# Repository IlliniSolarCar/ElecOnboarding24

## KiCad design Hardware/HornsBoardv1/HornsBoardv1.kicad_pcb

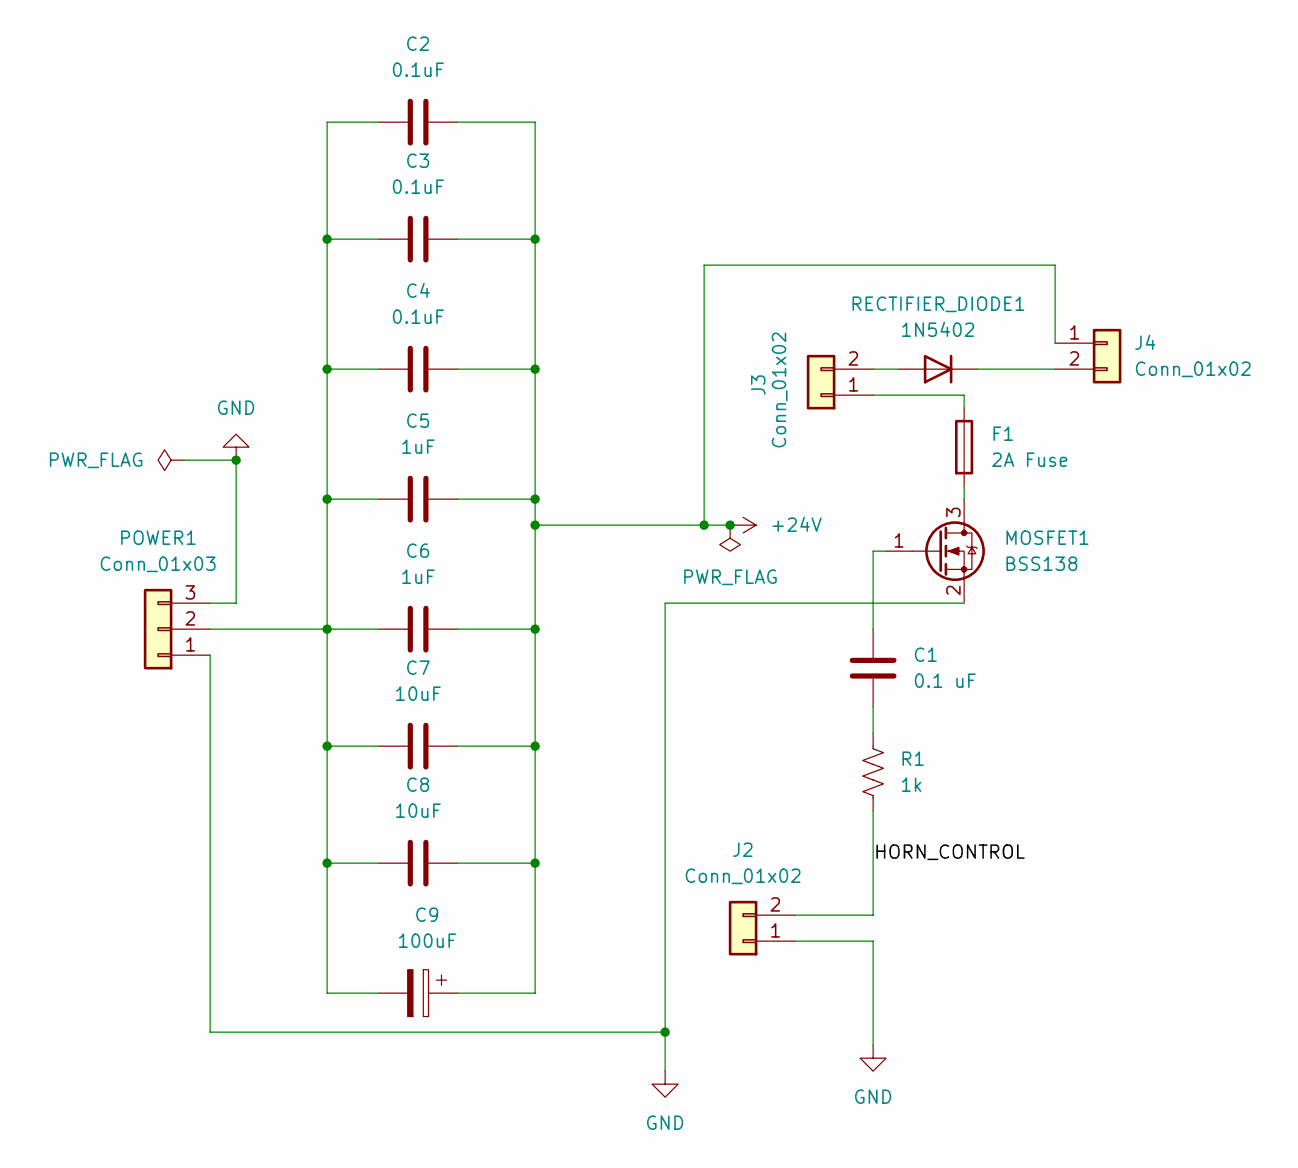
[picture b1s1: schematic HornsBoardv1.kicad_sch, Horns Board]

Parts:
C1: 0.1 uF; CP_Elec_6.3x3
C2, C3, C4: 0.1uF; CP_Elec_6.3x3
C5, C6: 1uF; CP_Elec_6.3x3
C7, C8: 10uF; CP_Elec_6.3x3
C9: 100uF; CP_Elec_6.3x3
F1: 2A Fuse; Fuse_0402_1005Metric_Pad0.77x0.64mm_HandSolder
J2, J3, J4: Conn_01x02; Molex_KK-254_AE-6410-02A_1x02_P2.54mm_Vertical
MOSFET1: BSS138; SOT-23
POWER1: Conn_01x03; Molex_KK-254_AE-6410-03A_1x03_P2.54mm_Vertical
R1: 1k; R_0603_1608Metric_Pad0.98x0.95mm_HandSolder
RECTIFIER_DIODE1: 1N5402; D_DO-201AD_P15.24mm_Horizontal; MPN 1N5402

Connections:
+24V: C2.2, C3.2, C4.2, C5.2, C6.2, C7.2, C8.2, C9.1, J4.1
/HORN_CONTROL: J2.2, R1.2
GND: J2.1, MOSFET1.2 (S), POWER1.1, POWER1.3
unnamed: C1.2, R1.1
unnamed: F1.1, J3.1
unnamed: J3.2, RECTIFIER_DIODE1.2 (A)
unnamed: J4.2, RECTIFIER_DIODE1.1 (K)
unnamed: F1.2, MOSFET1.3 (D)
unnamed: C1.1, MOSFET1.1 (G)
unnamed: C2.1, C3.1, C4.1, C5.1, C6.1, C7.1, C8.1, C9.2, POWER1.2

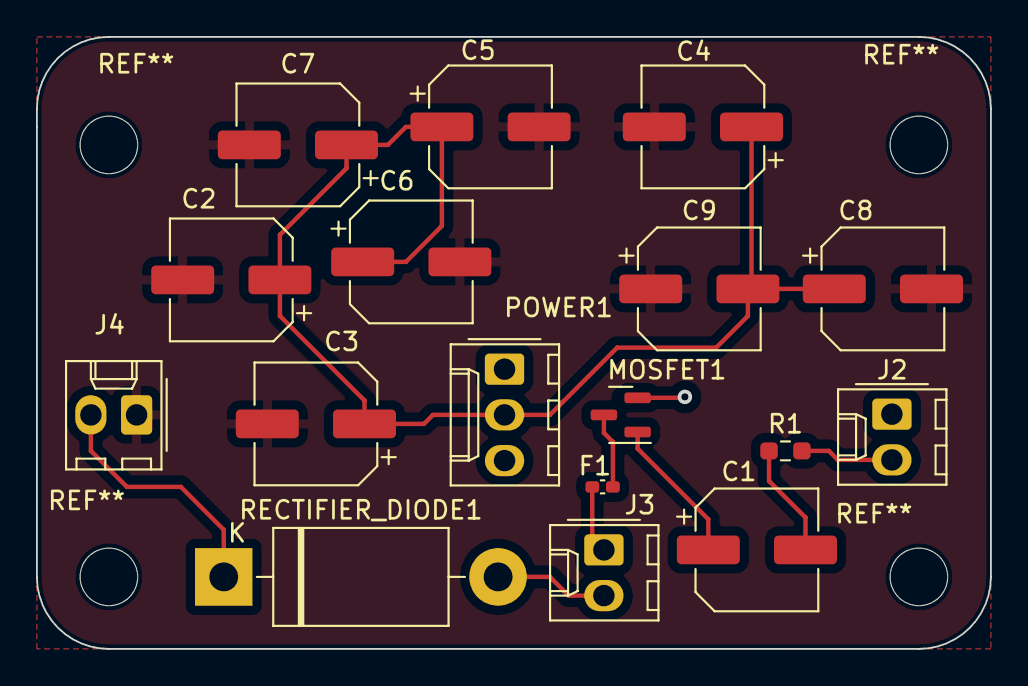
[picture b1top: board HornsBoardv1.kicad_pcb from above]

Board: 2 copper layers, 53.0 x 34.0 mm, 17 parts (0 on the bottom side), 10 nets.

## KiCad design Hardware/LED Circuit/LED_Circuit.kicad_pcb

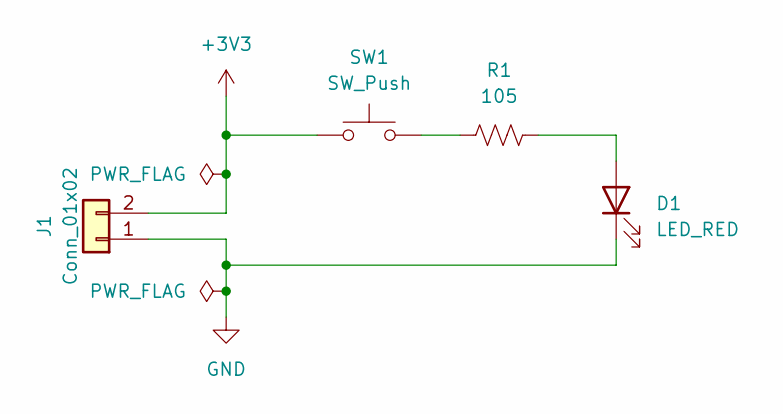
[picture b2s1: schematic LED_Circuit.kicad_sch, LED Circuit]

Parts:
D1: LED_RED; LED_0603_Symbol_on_F.SilkS
J1: Conn_01x02; Molex_KK-254_AE-6410-02A_1x02_P2.54mm_Vertical; MPN 022272021
R1: 105; R_0603_1608Metric_Pad0.98x0.95mm_HandSolder
SW1: SW_Push; SW_DIP_SPSTx01_Slide_6.7x4.1mm_W8.61mm_P2.54mm_LowProfile; MPN 1825910-6

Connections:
+3V3: J1.2, SW1.1
GND: D1.1 (K), J1.1
unnamed: D1.2 (A), R1.2
unnamed: R1.1, SW1.2

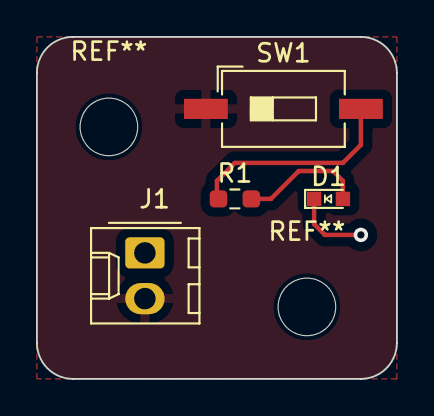
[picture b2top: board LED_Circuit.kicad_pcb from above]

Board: 2 copper layers, 20.0 x 19.0 mm, 4 parts (0 on the bottom side), 4 nets.

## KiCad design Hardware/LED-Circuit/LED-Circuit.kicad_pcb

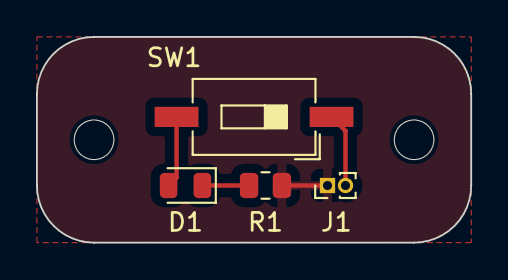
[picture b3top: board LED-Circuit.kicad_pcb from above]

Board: 2 copper layers, 24.1 x 11.4 mm, 4 parts (0 on the bottom side), 4 nets.

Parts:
D1: LED; D_0805_2012Metric
J1: Conn_01x02; PinHeader_1x02_P1.00mm_Vertical
R1: 220; R_0805_2012Metric
SW1: SW_Push; SW_DIP_SPSTx01_Slide_6.7x4.1mm_W8.61mm_P2.54mm_LowProfile

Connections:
+3.3V: J1.2, SW1.1
GND: J1.1, R1.2
unnamed: D1.2 (A), SW1.2
unnamed: D1.1 (K), R1.1
